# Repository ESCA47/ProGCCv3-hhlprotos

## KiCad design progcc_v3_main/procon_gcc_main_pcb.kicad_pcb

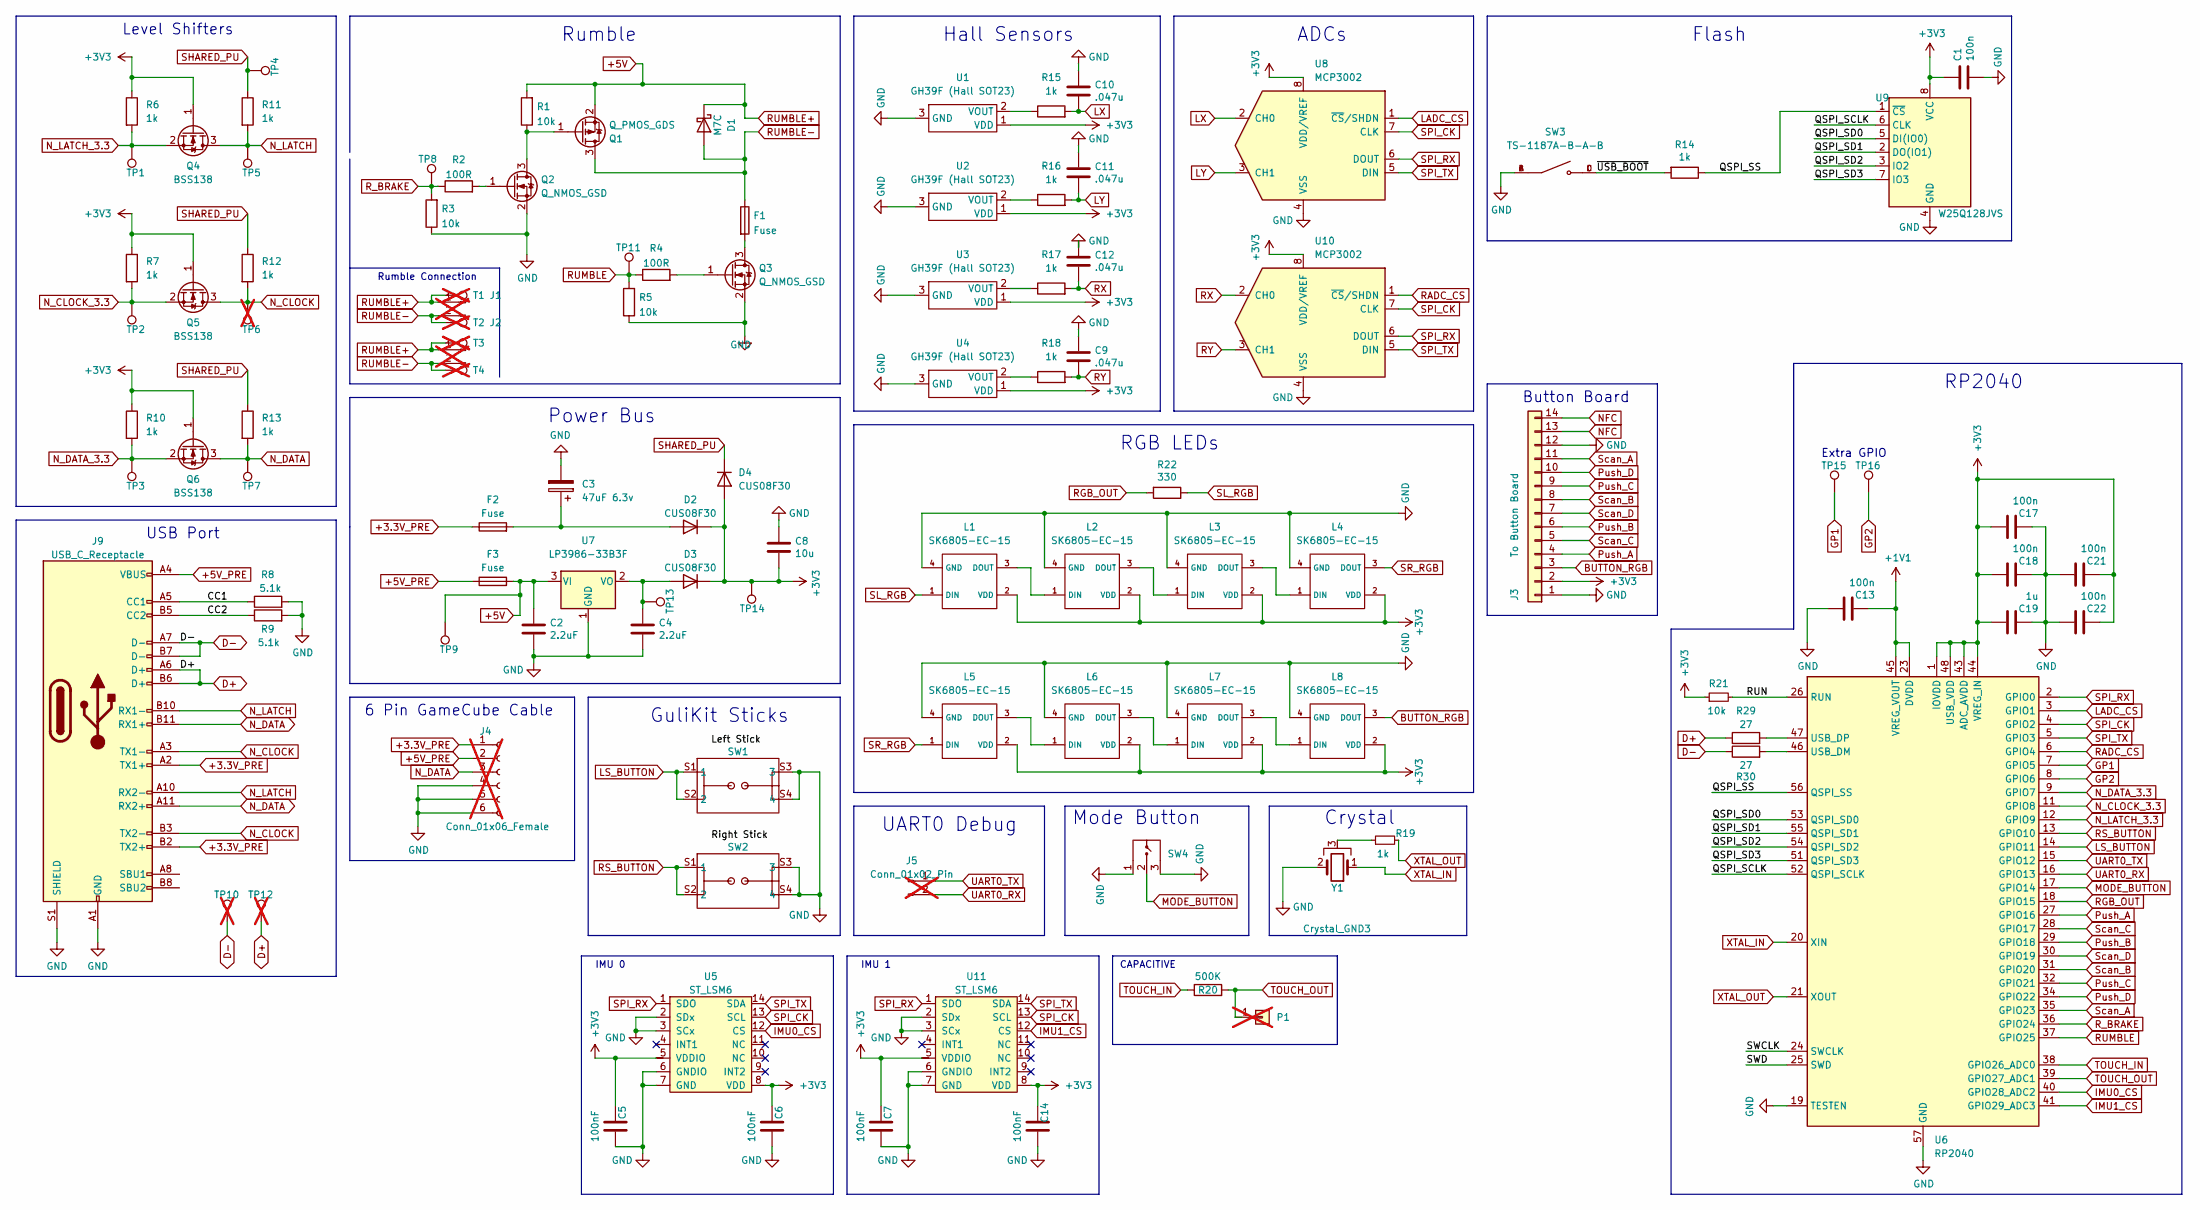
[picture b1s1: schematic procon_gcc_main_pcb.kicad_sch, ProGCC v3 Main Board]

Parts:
C1, C13, C17, C18, C21, C22: 100n; C_0402_1005Metric
C2, C4: 2.2uF; C_0603_1608Metric
C3: 47uF 6.3v; CP_EIA-3216-18_Kemet-A
C5, C6, C7, C14: 100nF; C_0603_1608Metric; LCSC C1525
C8: 10u; C_0603_1608Metric
C9, C10, C11, C12: .047u; C_0603_1608Metric_Pad1.08x0.95mm_HandSolder; LCSC C15849
C19: 1u; C_0402_1005Metric
D1: M7C; D_SOD-123; MPN B5819W SL; LCSC C8598
D2, D3, D4: CUS08F30; D_SOD-323_HandSoldering; MPN CUS08F30
F1, F2, F3: Fuse; Fuse_1206_3216Metric_Pad1.42x1.75mm_HandSolder; LCSC C69680
J1, J2: Rumble; rumble_pins; not fitted
J3: To Button Board; molex_5051101492_14P; MPN molex_5051101492_14P
J4: Conn_01x06_Female; GCC_Header_Straight_1x06_Pitch2.00mm; not fitted
J5: Conn_01x02_Pin; PinHeader_1x02_P2.00mm_Vertical; not fitted
J9: USB_C_Receptacle; Shou Han Type-C 24P QCHT; MPN Shou Han Type-C 24P QCHT
L1, L2, L3, L4, L5, L6, L7, L8: SK6805-EC-15; MPN SK6805-EC-15
P1: Endpoint; PinHeader_1x01_P2.54mm_Vertical; not fitted
Q1: Q_PMOS_GDS; SOT-23; MPN AO3401A; LCSC C15127
Q2, Q3: Q_NMOS_GSD; SOT-23; MPN AO3400A; LCSC C20917
Q4, Q5, Q6: BSS138; SOT-23; MPN BSS138
R1, R3, R5: 10k; R_0402_1005Metric; LCSC C25804
R2, R4: 100R; R_0402_1005Metric; LCSC C22775
R6, R7, R10, R11, R12, R13: 1k; R_0603_1608Metric_Pad0.98x0.95mm_HandSolder
R8, R9: 5.1k; R_0603_1608Metric_Pad0.98x0.95mm_HandSolder
R14, R15, R16, R17, R18, R19: 1k; R_0402_1005Metric
R20: 500K; R_0402_1005Metric; LCSC C11616
R21: 10k; R_0402_1005Metric
R22: 330; R_0402_1005Metric
R29, R30: 27; R_0402_1005Metric
SW1, SW2: GL18_SW; GL18; MPN GL18
SW3: TS-1187A-B-A-B; SW_TS-1187A-B-A-B; PARTREV A0
SW4: TS35CA; MPN TS35CA
T1, T2, T3, T4: 36-8730; KS_8730; not fitted
TP1, TP2, TP3, TP4, TP5, TP7, TP8, TP9, TP11, TP13, TP14, TP15, TP16: TestPoint; TestPoint_Pad_D1.5mm
TP6, TP10, TP12: TestPoint; TestPoint_Pad_D1.5mm; not fitted
U1, U2, U3, U4: GH39F (Hall SOT23); GH39F; MPN GH39F
U5, U11: ST_LSM6; LGA14; MPN LSM6DSRTR; LCSC C784817
U6: RP2040; QFN-56-1EP_7x7mm_P0.4mm_EP3.2x3.2mm; MPN RP2040
U7: LP3986-33B3F; SOT-23; MPN LP3986-33B3F; LCSC Part Number C387689
U8, U10: MCP3002; SOIC-8_3.9x4.9mm_P1.27mm; MPN MCP3002
U9: W25Q128JVS; SOIC-8_5.23x5.23mm_P1.27mm; MPN W25Q128JVS
Y1: Crystal_GND3; Resonator_SMD_Murata_CSTxExxV-3Pin_3.0x1.1mm; MPN CSTNE12M0GH5L000R0

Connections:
+1V1: C13.2, U6.23 (DVDD), U6.45 (VREG_VOUT), U6.50 (DVDD)
+3.3V_PRE: F2.1, J4.1, J9.A2 (TX1+), J9.B2 (TX2+)
+3V3: C1.1, C5.2, C6.2, C7.2, C8.2, C14.2, C17.1, C18.1, C19.1, C21.2, C22.2, D2.1 (K), D3.1 (K), D4.2 (A), J3.2, L1.2 (VDD), L2.2 (VDD), L3.2 (VDD), L4.2 (VDD), L5.2 (VDD), L6.2 (VDD), L7.2 (VDD), L8.2 (VDD), Q4.1 (G), Q5.1 (G), Q6.1 (G), R6.1, R7.1, R10.1, R21.1, TP14.1, U1.1 (VDD), U2.1 (VDD), U3.1 (VDD), U4.1 (VDD), U5.5 (VDDIO), U5.8 (VDD), U6.1 (IOVDD), U6.10 (IOVDD), U6.22 (IOVDD), U6.33 (IOVDD), U6.42 (IOVDD), U6.43 (ADC_AVDD), U6.44 (VREG_IN), U6.48 (USB_VDD), U6.49 (IOVDD), U8.8 (VDD/VREF), U9.8 (VCC), U10.8 (VDD/VREF), U11.5 (VDDIO), U11.8 (VDD)
+5V: C2.1, D1.1 (K), F3.2, J1.1, J2.1, Q1.2 (S), R1.2, T1.1, T3.1, TP9.1, U7.3 (VI)
+5V_PRE: F3.1, J4.2, J9.A4 (VBUS), J9.A9 (VBUS), J9.B4 (VBUS), J9.B9 (VBUS)
/CC1: J9.A5 (CC1), R8.1
/CC2: J9.B5 (CC2), R9.1
/QSPI_SCLK: U6.52 (QSPI_SCLK), U9.6 (CLK)
/QSPI_SD0: U6.53 (QSPI_SD0), U9.5 (DI(IO0))
/QSPI_SD1: U6.55 (QSPI_SD1), U9.2 (DO(IO1))
/QSPI_SD2: U6.54 (QSPI_SD2), U9.3 (IO2)
/QSPI_SD3: U6.51 (QSPI_SD3), U9.7 (IO3)
/QSPI_SS: R14.1, U6.56 (QSPI_SS), U9.1 (~CS)
/RUN: R21.2, U6.26 (RUN)
/SWCLK: U6.24 (SWCLK)
/SWD: U6.25 (SWD)
/~USB_BOOT: R14.2, SW3.C, SW3.D
BUTTON_RGB: J3.3, L8.3 (DOUT)
D+: J9.A6 (D+), J9.B6 (D+), R29.1, TP12.1
D-: J9.A7 (D-), J9.B7 (D-), R30.1, TP10.1
GND: C1.2, C2.2, C3.2, C4.2, C5.1, C6.1, C7.1, C8.1, C9.1, C10.1, C11.1, C12.1, C13.1, C14.1, C17.2, C18.2, C19.2, C21.1, C22.1, J3.1, J3.12, J4.4, J4.5, J4.6, J9.A1 (GND), J9.A12 (GND), J9.B1 (GND), J9.B12 (GND), J9.S1 (SHIELD), L1.4 (GND), L2.4 (GND), L3.4 (GND), L4.4 (GND), L5.4 (GND), L6.4 (GND), L7.4 (GND), L8.4 (GND), Q2.2 (S), Q3.2 (S), R3.1, R5.1, R8.2, R9.2, SW1.S3 (3), SW1.S4 (4), SW2.S3 (3), SW2.S4 (4), SW3.A, SW3.B, SW4.1, SW4.3, U1.3 (GND), U2.3 (GND), U3.3 (GND), U4.3 (GND), U5.2 (SDx), U5.3 (SCx), U5.6 (GNDIO), U5.7 (GND), U6.19 (TESTEN), U6.57 (GND), U7.1 (GND), U8.4 (VSS), U9.4 (GND), U10.4 (VSS), U11.2 (SDx), U11.3 (SCx), U11.6 (GNDIO), U11.7 (GND), Y1.2
GP1: TP15.1, U6.7 (GPIO5)
GP2: TP16.1, U6.8 (GPIO6)
IMU0_CS: U5.12 (CS), U6.40 (GPIO28_ADC2)
IMU1_CS: U6.41 (GPIO29_ADC3), U11.12 (CS)
LADC_CS: U6.3 (GPIO1), U8.1 (~CS/SHDN)
LS_BUTTON: SW1.S1 (1), SW1.S2 (2), U6.14 (GPIO11)
LX: C10.2, R15.2, U8.2 (CH0)
LY: C11.2, R16.2, U8.3 (CH1)
MODE_BUTTON: SW4.2, U6.17 (GPIO14)
NFC: J3.13, J3.14
N_CLOCK: J9.A3 (TX1-), J9.B3 (TX2-), Q5.3 (D), R12.2, TP6.1
N_CLOCK_3.3: Q5.2 (S), R7.2, TP2.1, U6.11 (GPIO8)
N_DATA: J4.3, J9.A11 (RX2+), J9.B11 (RX1+), Q6.3 (D), R13.2, TP7.1
N_DATA_3.3: Q6.2 (S), R10.2, TP3.1, U6.9 (GPIO7)
N_LATCH: J9.A10 (RX2-), J9.B10 (RX1-), Q4.3 (D), R11.2, TP5.1
N_LATCH_3.3: Q4.2 (S), R6.2, TP1.1, U6.12 (GPIO9)
unnamed: C3.1, D2.2 (A), F2.2
unnamed: C4.1, D3.2 (A), TP13.1, U7.2 (VO)
unnamed: L1.3 (DOUT), L2.1 (DIN)
unnamed: L2.3 (DOUT), L3.1 (DIN)
unnamed: L3.3 (DOUT), L4.1 (DIN)
unnamed: L5.3 (DOUT), L6.1 (DIN)
unnamed: L6.3 (DOUT), L7.1 (DIN)
unnamed: L7.3 (DOUT), L8.1 (DIN)
unnamed: Q1.1 (G), Q2.3 (D), R1.1
unnamed: Q2.1 (G), R2.2
unnamed: F1.2, Q3.3 (D)
unnamed: Q3.1 (G), R4.2
unnamed: R19.1, Y1.3
unnamed: R15.1, U1.2 (VOUT)
unnamed: R16.1, U2.2 (VOUT)
unnamed: R17.1, U3.2 (VOUT)
unnamed: R18.1, U4.2 (VOUT)
unnamed: R30.2, U6.46 (USB_DM)
unnamed: R29.2, U6.47 (USB_DP)
Push_A: J3.4, U6.27 (GPIO16)
Push_B: J3.6, U6.29 (GPIO18)
Push_C: J3.9, U6.32 (GPIO21)
Push_D: J3.10, U6.34 (GPIO22)
RADC_CS: U6.6 (GPIO4), U10.1 (~CS/SHDN)
RGB_OUT: R22.2, U6.18 (GPIO15)
RS_BUTTON: SW2.S1 (1), SW2.S2 (2), U6.13 (GPIO10)
RUMBLE: R4.1, R5.2, TP11.1, U6.37 (GPIO25)
RUMBLE-: D1.2 (A), F1.1, J1.2, J2.2, Q1.3 (D), T2.1, T4.1
RX: C12.2, R17.2, U10.2 (CH0)
RY: C9.2, R18.2, U10.3 (CH1)
R_BRAKE: R2.1, R3.2, TP8.1, U6.36 (GPIO24)
SHARED_PU: D4.1 (K), R11.1, R12.1, R13.1, TP4.1
SL_RGB: L1.1 (DIN), R22.1
SPI_CK: U5.13 (SCL), U6.4 (GPIO2), U8.7 (CLK), U10.7 (CLK), U11.13 (SCL)
SPI_RX: U5.1 (SDO), U6.2 (GPIO0), U8.6 (DOUT), U10.6 (DOUT), U11.1 (SDO)
SPI_TX: U5.14 (SDA), U6.5 (GPIO3), U8.5 (DIN), U10.5 (DIN), U11.14 (SDA)
SR_RGB: L4.3 (DOUT), L5.1 (DIN)
Scan_A: J3.11, U6.35 (GPIO23)
Scan_B: J3.8, U6.31 (GPIO20)
Scan_C: J3.5, U6.28 (GPIO17)
Scan_D: J3.7, U6.30 (GPIO19)
TOUCH_IN: R20.1, U6.38 (GPIO26_ADC0)
TOUCH_OUT: P1.1, R20.2, U6.39 (GPIO27_ADC1)
UART0_RX: J5.2, U6.16 (GPIO13)
UART0_TX: J5.1, U6.15 (GPIO12)
XTAL_IN: U6.20 (XIN), Y1.1
XTAL_OUT: R19.2, U6.21 (XOUT)

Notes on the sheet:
Flash
Crystal
IMU 1
Button Board
CAPACITIVE
Extra GPIO
Rumble Connection
IMU 0
RGB LEDs
RP2040
UART0 Debug
GuliKit Sticks
Hall Sensors
Mode Button
Power Bus
ADCs
Level Shifters
Rumble
USB Port
6 Pin GameCube Cable

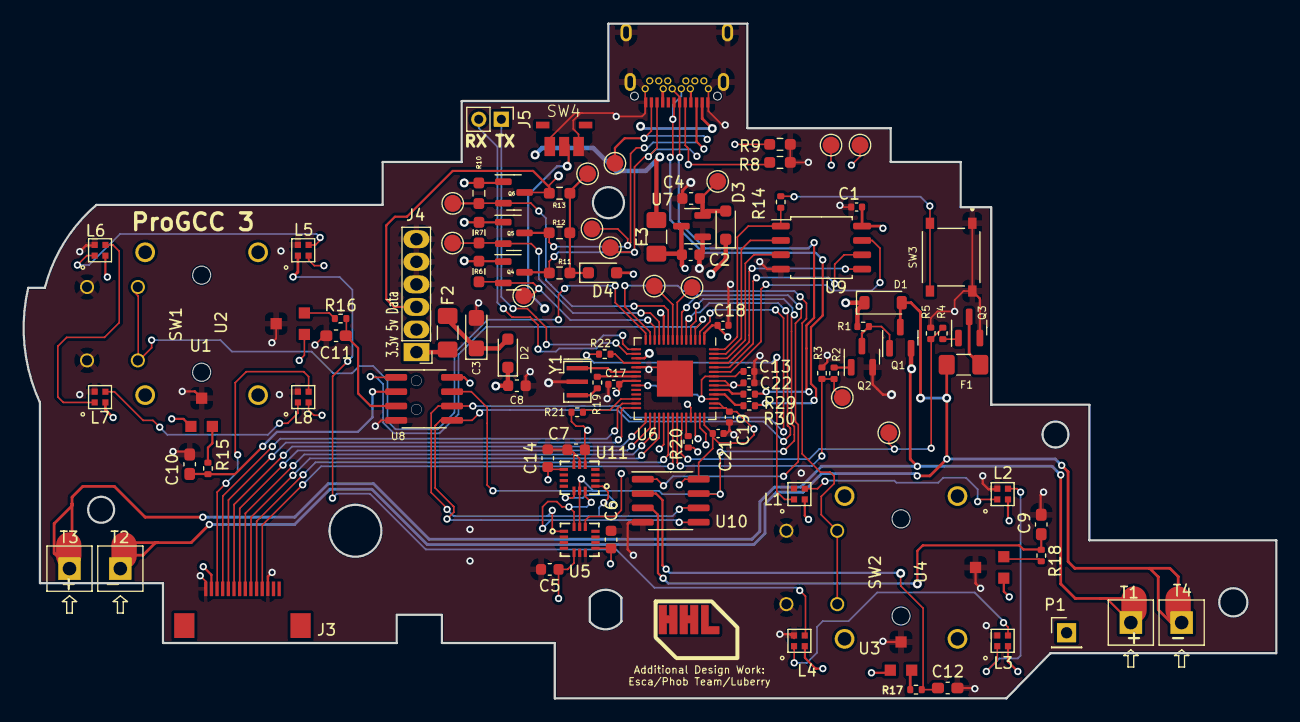
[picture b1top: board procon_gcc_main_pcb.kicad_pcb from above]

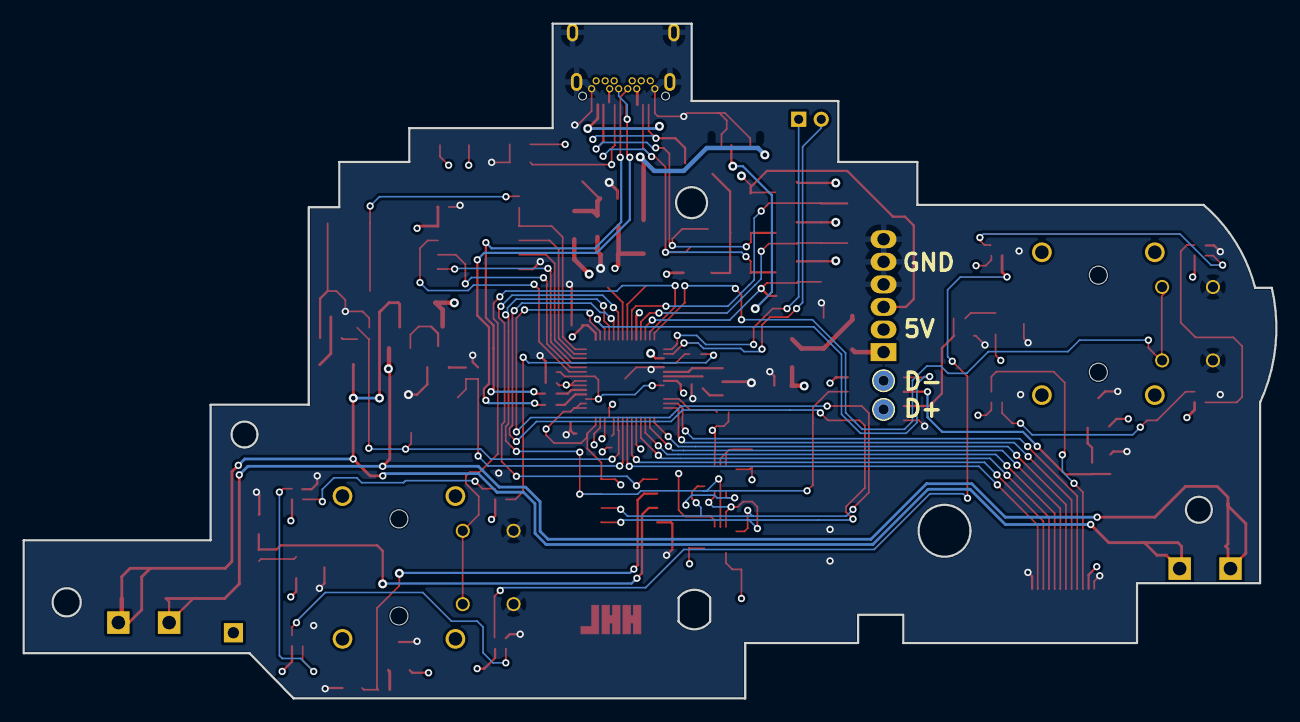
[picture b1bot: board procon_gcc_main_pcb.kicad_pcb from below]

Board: 4 copper layers, 110.9 x 59.7 mm, 107 parts (2 on the bottom side), 82 nets.

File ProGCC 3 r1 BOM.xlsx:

# | Reference | Qty | Value | Footprint | DNP | MPN
1.0 | C1, C13, C17, C18, C21, C22 | 6.0 | 100n | Capacitor_SMD:C_0402_1005Metric
2.0 | C2, C4 | 2.0 | 2.2uF | Capacitor_SMD:C_0603_1608Metric
3.0 | C3 | 1.0 | 47uF 6.3v | Capacitor_Tantalum_SMD:CP_EIA-3216-18_Kemet-A
4.0 | C5, C6, C7, C14 | 4.0 | 100nF | Capacitor_SMD:C_0603_1608Metric
5.0 | C8 | 1.0 | 10u | Capacitor_SMD:C_0603_1608Metric
6.0 | C9, C10, C11, C12 | 4.0 | .047u | Capacitor_SMD:C_0603_1608Metric_Pad1.08x0.95mm_HandSolder
7.0 | C19 | 1.0 | 1u | Capacitor_SMD:C_0402_1005Metric
8.0 | D1 | 1.0 | M7C | Diode_SMD:D_SOD-123 |  | B5819W SL
9.0 | D2, D3, D4 | 3.0 | CUS08F30 | Diode_SMD:D_SOD-323_HandSoldering |  | CUS08F30
10.0 | F1, F2, F3 | 3.0 | Fuse | Fuse:Fuse_1206_3216Metric_Pad1.42x1.75mm_HandSolder
11.0 | J1, J2 | 2.0 | Rumble | progcc_v3:rumble_pins | DNP
12.0 | J3 | 1.0 | To Button Board | progcc_v3:molex_5051101492_14P |  | molex_5051101492_14P
13.0 | J9 | 1.0 | USB_C_Receptacle | progcc_v3:Shou Han Type-C 24P QCHT |  | Shou Han Type-C 24P QCHT
14.0 | L1, L2, L3, L4, L5, L6, L7, L8 | 8.0 | SK6805-EC-15 | progcc_v3:SK6805-EC-15 |  | SK6805-EC-15
15.0 | P1 | 1.0 | Endpoint | Connector_PinHeader_2.54mm:PinHeader_1x01_P2.54mm_Vertical | DNP
16.0 | Q1 | 1.0 | Q_PMOS_GDS | Package_TO_SOT_SMD:SOT-23 |  | AO3401A
17.0 | Q2, Q3 | 2.0 | Q_NMOS_GSD | Package_TO_SOT_SMD:SOT-23 |  | AO3400A
18.0 | Q4, Q5, Q6 | 3.0 | BSS138 | Package_TO_SOT_SMD:SOT-23 |  | BSS138
19.0 | R1, R3, R5, R21 | 4.0 | 10k | Resistor_SMD:R_0402_1005Metric
20.0 | R2, R4 | 2.0 | 100R | Resistor_SMD:R_0402_1005Metric
21.0 | R6, R7, R10, R11, R12, R13 | 6.0 | 1k | Resistor_SMD:R_0603_1608Metric_Pad0.98x0.95mm_HandSolder
22.0 | R8, R9 | 2.0 | 5.1k | Resistor_SMD:R_0603_1608Metric_Pad0.98x0.95mm_HandSolder
23.0 | R14, R15, R16, R17, R18, R19 | 6.0 | 1k | Resistor_SMD:R_0402_1005Metric
24.0 | R20 | 1.0 | 500K | Resistor_SMD:R_0402_1005Metric
25.0 | R22 | 1.0 | 330.0 | Resistor_SMD:R_0402_1005Metric
26.0 | R29, R30 | 2.0 | 27.0 | Resistor_SMD:R_0402_1005Metric
27.0 | SW1, SW2 | 2.0 | GL18_SW | progcc_v3:GL18 |  | GL18
28.0 | SW3 | 1.0 | TS-1187A-B-A-B | progcc_v3:SW_TS-1187A-B-A-B |  | TS-1187A-B-A-B
29.0 | SW4 | 1.0 | ~ | progcc_v3:TS35CA |  | TS35CA
30.0 | T1, T2, T3, T4 | 4.0 | 36-8730 | progcc_v3:KS_8730 | DNP
31.0 | TP1, TP2, TP3, TP4, TP5, TP6, TP7, TP8, TP9, TP10, TP11, TP12, TP13, TP14, TP15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 | 16.0 | TestPoint | TestPoint:TestPoint_Pad_D1.5mm | DNP
32.0 | U1, U2, U3, U4 | 4.0 | GH39F (Hall SOT23) | progcc_v3:GH39F |  | GH39F
33.0 | U5, U11 | 2.0 | ST_LSM6 | progcc_v3:LGA14 |  | LSM6DSRTR
34.0 | U6 | 1.0 | RP2040 | Package_DFN_QFN:QFN-56-1EP_7x7mm_P0.4mm_EP3.2x3.2mm |  | RP2040
35.0 | U7 | 1.0 | LP3986-33B3F | Package_TO_SOT_SMD:SOT-23
36.0 | U8, U10 | 2.0 | MCP3002 | progcc_v3:SOIC-8_3.9x4.9mm_P1.27mm |  | MCP3002
37.0 | U9 | 1.0 | W25Q128JVS | Package_SO:SOIC-8_5.23x5.23mm_P1.27mm |  | W25Q128JVS
38.0 | Y1 | 1.0 | Crystal_GND3 | Crystal:Resonator_SMD_Murata_CSTxExxV-3Pin_3.0x1.1mm |  | CSTNE12M0GH5L000R0

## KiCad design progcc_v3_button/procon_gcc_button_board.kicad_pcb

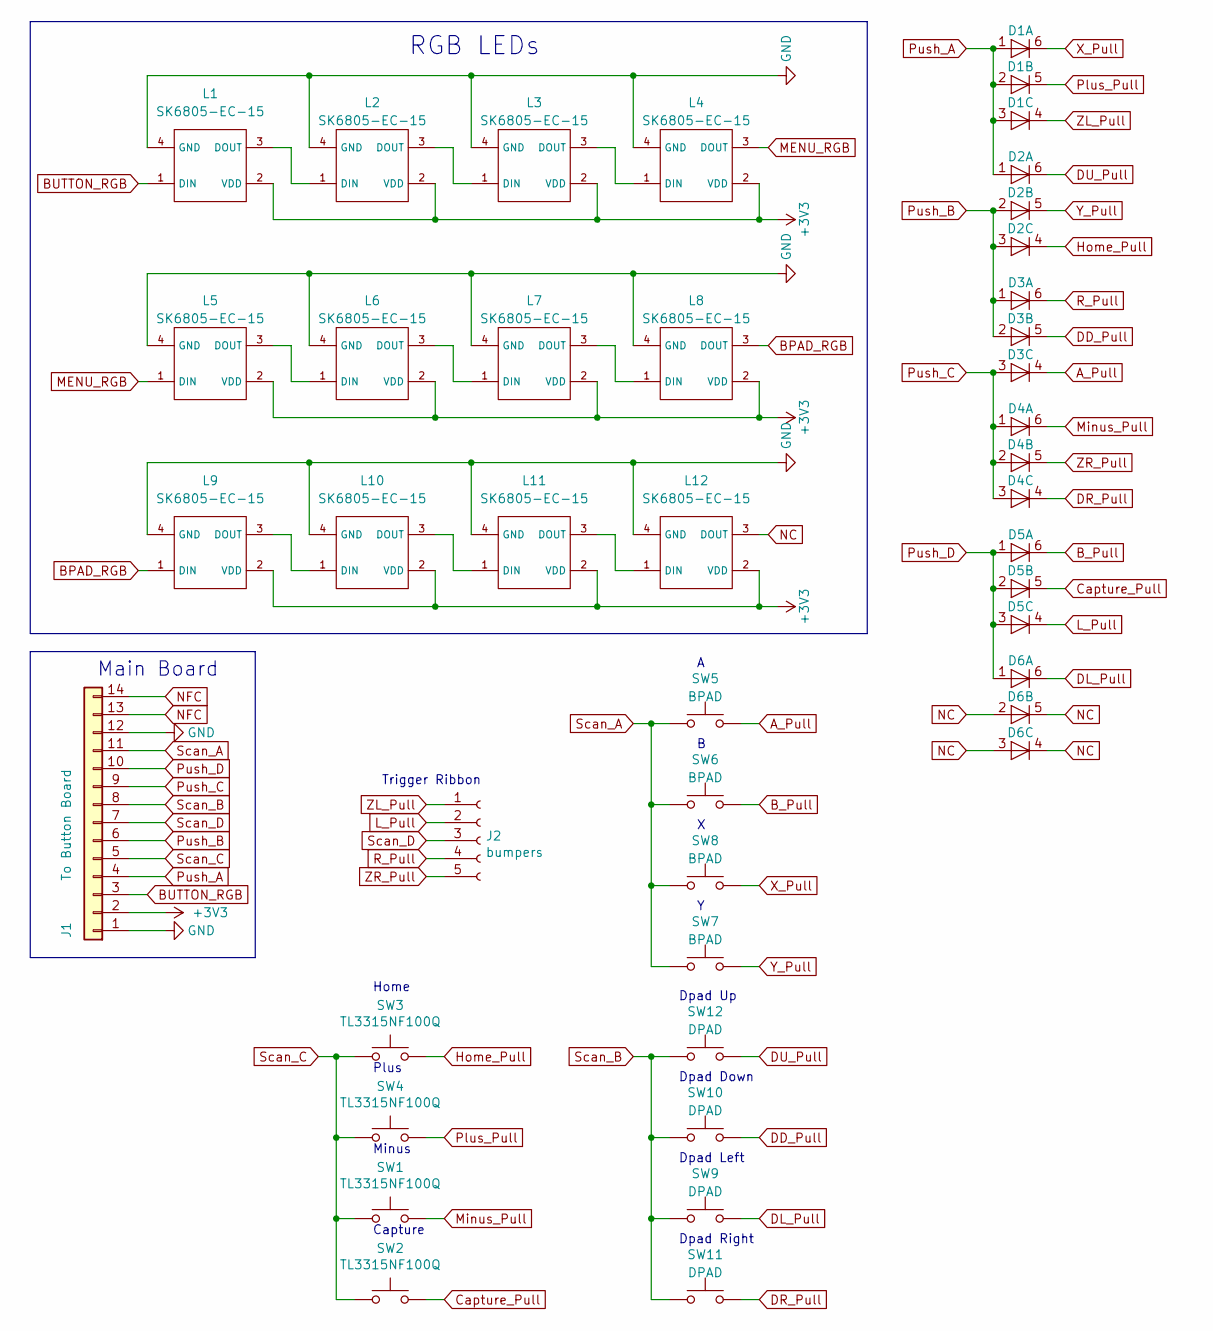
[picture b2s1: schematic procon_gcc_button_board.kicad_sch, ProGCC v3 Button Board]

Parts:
D1, D2, D3, D4, D5, D6: BAS16VY,115; SOT-363_SC-70-6
J1: To Button Board; molex_5051101492_14P
J2: bumpers; molex_5034800540
L1, L2, L3, L4, L5, L6, L7, L8, L9, L10, L11, L12: SK6805-EC-15
SW1, SW2, SW3, SW4: TL3315NF100Q; TL3315NFxxxQ
SW5, SW6, SW7, SW8: BPAD; progcc_bpad
SW9, SW10, SW11, SW12: DPAD; progcc_dpad

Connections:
+3V3: J1.2, L1.2 (VDD), L2.2 (VDD), L3.2 (VDD), L4.2 (VDD), L5.2 (VDD), L6.2 (VDD), L7.2 (VDD), L8.2 (VDD), L9.2 (VDD), L10.2 (VDD), L11.2 (VDD), L12.2 (VDD)
A_Pull: D3.4 (K), SW5.2
BPAD_RGB: L8.3 (DOUT), L9.1 (DIN)
BUTTON_RGB: J1.3, L1.1 (DIN)
B_Pull: D5.6 (K), SW6.2
Capture_Pull: D5.5 (K), SW2.3, SW2.4
DD_Pull: D3.5 (K), SW10.2
DL_Pull: D6.6 (K), SW9.2
DR_Pull: D4.4 (K), SW11.2
DU_Pull: D2.6 (K), SW12.2
GND: J1.1, J1.12, L1.4 (GND), L2.4 (GND), L3.4 (GND), L4.4 (GND), L5.4 (GND), L6.4 (GND), L7.4 (GND), L8.4 (GND), L9.4 (GND), L10.4 (GND), L11.4 (GND), L12.4 (GND)
Home_Pull: D2.4 (K), SW3.3, SW3.4
L_Pull: D5.4 (K), J2.2
MENU_RGB: L4.3 (DOUT), L5.1 (DIN)
Minus_Pull: D4.6 (K), SW1.3, SW1.4
NC: D6.2 (A), D6.3 (A), D6.4 (K), D6.5 (K), L12.3 (DOUT)
NFC: J1.13, J1.14
unnamed: L1.3 (DOUT), L2.1 (DIN)
unnamed: L2.3 (DOUT), L3.1 (DIN)
unnamed: L3.3 (DOUT), L4.1 (DIN)
unnamed: L5.3 (DOUT), L6.1 (DIN)
unnamed: L6.3 (DOUT), L7.1 (DIN)
unnamed: L7.3 (DOUT), L8.1 (DIN)
unnamed: L9.3 (DOUT), L10.1 (DIN)
unnamed: L10.3 (DOUT), L11.1 (DIN)
unnamed: L11.3 (DOUT), L12.1 (DIN)
Plus_Pull: D1.5 (K), SW4.3, SW4.4
Push_A: D1.1 (A), D1.2 (A), D1.3 (A), D2.1 (A), J1.4
Push_B: D2.2 (A), D2.3 (A), D3.1 (A), D3.2 (A), J1.6
Push_C: D3.3 (A), D4.1 (A), D4.2 (A), D4.3 (A), J1.9
Push_D: D5.1 (A), D5.2 (A), D5.3 (A), D6.1 (A), J1.10
R_Pull: D3.6 (K), J2.4
Scan_A: J1.11, SW5.1, SW6.1, SW7.1, SW8.1
Scan_B: J1.8, SW9.1, SW10.1, SW11.1, SW12.1
Scan_C: J1.5, SW1.1, SW1.2, SW2.1, SW2.2, SW3.1, SW3.2, SW4.1, SW4.2
Scan_D: J1.7, J2.3
X_Pull: D1.6 (K), SW8.2
Y_Pull: D2.5 (K), SW7.2
ZL_Pull: D1.4 (K), J2.1
ZR_Pull: D4.5 (K), J2.5

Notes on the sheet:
Plus
Capture
Dpad Right
Main Board
Dpad Up
Dpad Down
Trigger Ribbon
Dpad Left
Home
Minus
RGB LEDs

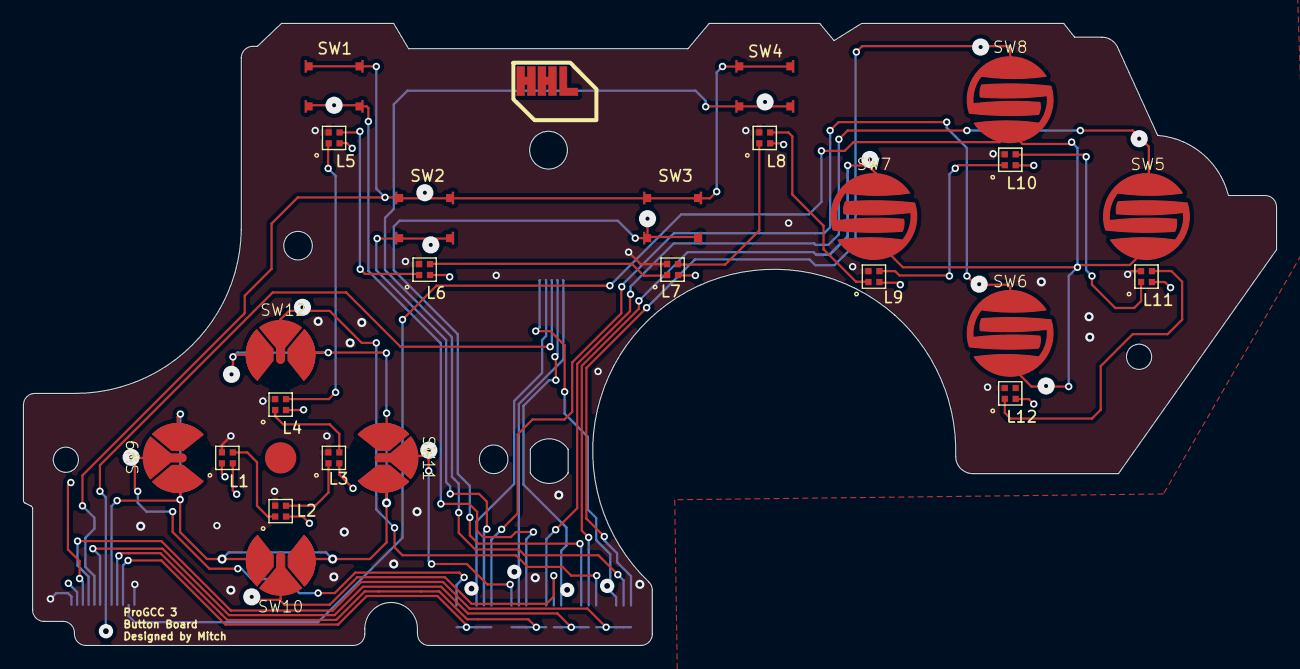
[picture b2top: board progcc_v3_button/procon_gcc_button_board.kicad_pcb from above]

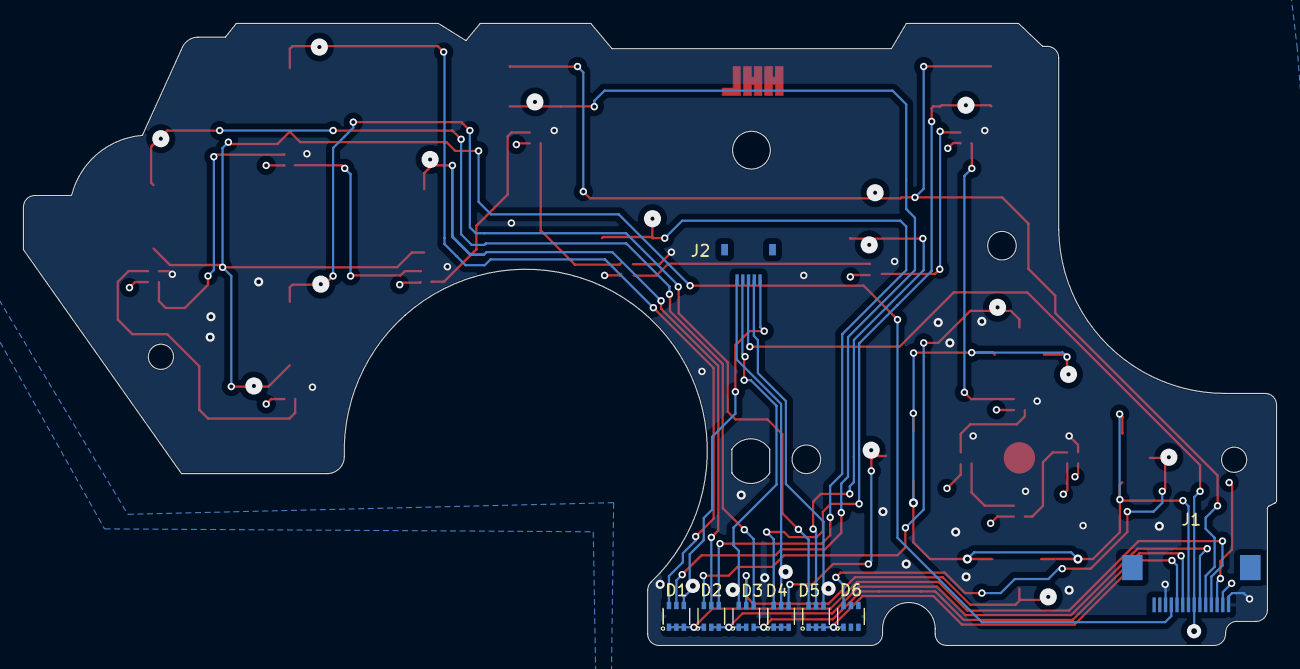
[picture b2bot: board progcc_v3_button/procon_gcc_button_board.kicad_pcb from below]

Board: 4 copper layers, 109.4 x 54.3 mm, 32 parts (8 on the bottom side), 40 nets.

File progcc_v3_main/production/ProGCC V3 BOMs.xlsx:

Id | Designator | Footprint | Quantity | Designation | Supplier and ref | Part # | Notes
1.0 | SW4,SW2,SW1,SW3 | TL3315NFxxxQ | 4.0 | TL3315NF100Q |  | TL3315NF100Q
2.0 | L6,L4,L2,L12,L5,L9,L1,L3,L11,L7,L10,L8 | SK6805-EC-15 | 12.0 | SK6805-EC-15 |  | SK6805-EC-15
3.0 | SW7,SW5,SW6,SW8 | progcc_bpad | 4.0 | BPAD |  |  | DNP no solder.
4.0 | D2,D5,D4,D6,D3,D1 | SOT-363_SC-70-6 | 6.0 | BAS16VY,115 |  | BAS16VY,115
5.0 | J2 | molex_5051100592_5P | 1.0 | bumpers |  | molex_5051100592_5P
6.0 | J1 | molex_5051101492_14P | 1.0 | To Button Board |  | molex_5051101492_14P

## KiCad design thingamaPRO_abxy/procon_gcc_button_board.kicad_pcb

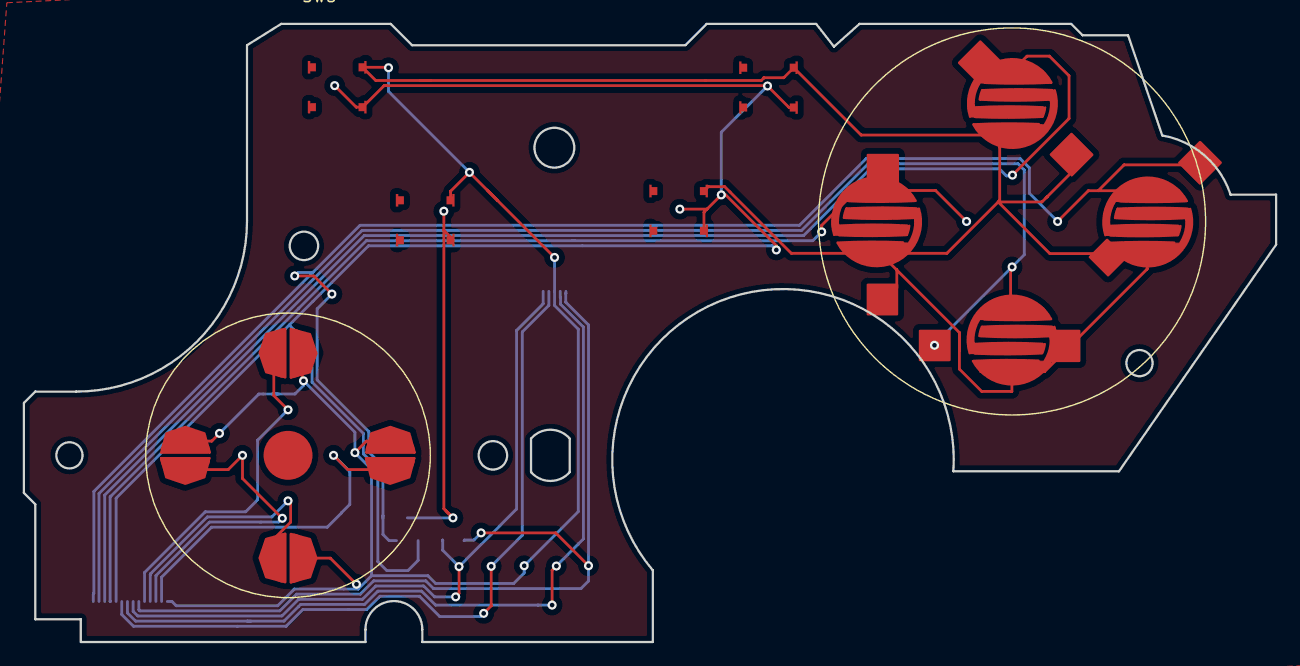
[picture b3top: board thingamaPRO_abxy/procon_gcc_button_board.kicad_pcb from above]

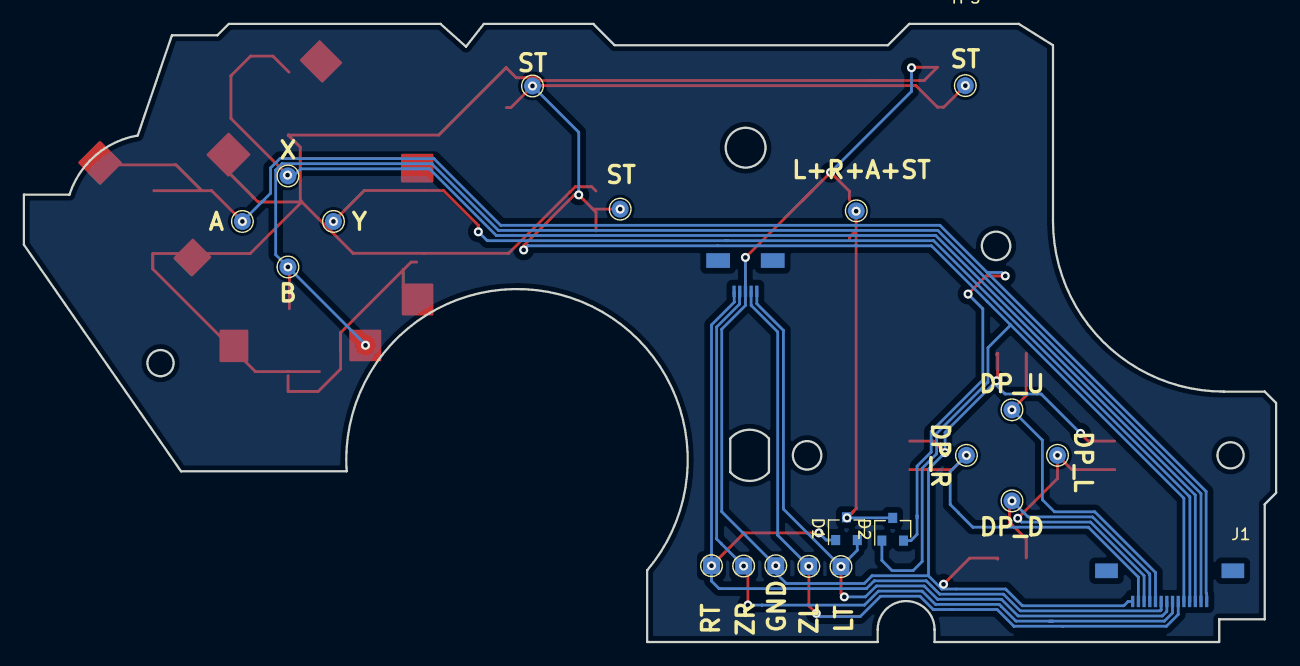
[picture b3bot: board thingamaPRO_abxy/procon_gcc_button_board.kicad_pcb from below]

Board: 2 copper layers, 110.0 x 54.3 mm, 31 parts (21 on the bottom side), 15 nets.

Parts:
D1, D2: BAV70; SOT-23
J1: Button Board; molex_5051101492_14P
J2: bumpers; molex_5051100592_5P
Ref**: Val**; ABXY_Contact_Omron_Switch
Ref**#2, Ref**#3, Ref**#4: Val**; ABXY_Contact_Omron_Switch
SW1: procon_abxy
SW2: procon_dpad
SW3, SW4, SW5, SW6: TL3315NF100Q; TL3315NFxxxQ
TP1, TP2, TP3, TP4, TP5, TP5#2, TP5#3, TP5#4, TP6, TP7, TP8, TP9, TP10, TP11, TP12, TP13, TP14: TestPoint; TestPoint_Pad_D1.5mm

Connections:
BB_BTN_A: D2.2 (A), J1.1, Ref**#4.2, SW1.1 (A), TP1.1
BB_BTN_B: J1.2, Ref**.2, SW1.2 (B), TP2.1
BB_BTN_DP_D: J1.11, SW2.3 (DP_D), TP11.1
BB_BTN_DP_L: J1.12, SW2.4 (DP_L), TP12.1
BB_BTN_DP_R: J1.13, SW2.2 (DP_R), TP13.1
BB_BTN_DP_U: J1.10, SW2.1 (DP_U), TP10.1
BB_BTN_LT: D1.2 (A), J1.8, J2.1, TP8.1
BB_BTN_RT: D1.1 (A), J1.9, J2.5, TP9.1
BB_BTN_ST: D2.1 (A), J1.5, SW3.1, SW5.1, SW6.1, TP5.1, TP5#2.1, TP5#3.1, TP5#4.1
BB_BTN_X: J1.3, SW1.4 (X), TP3.1
BB_BTN_Y: J1.4, SW1.3 (Y), TP4.1
BB_BTN_ZL: J1.6, J2.2, TP6.1
BB_BTN_ZR: J1.7, J2.4, TP7.1
GND: J1.14, J2.3, Ref**#2.2, Ref**#3.2, SW1.GND, SW2.GND, SW3.2, SW4.2, SW5.2, SW6.2, TP14.1
unnamed: D1.3 (K), D2.3 (K), SW4.1

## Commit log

2023-03-06 copypastefromdesktop
2023-03-09 added screw in terminals
    pushing this to have a branch before the mapping changes
2023-03-09 Matrix Rewire for front boards
    Swapped from direct to a matrix layout to support oem front boards
2023-03-11 Update naming schema
2023-03-11 Update gitignore
2023-03-11 Remove backups
2023-03-11 all libraries fixed+hole positioning changes
    fixed the screw points to be more accurate as well add a front bracket keepout to help with the future reroute
2023-03-19 Moved components+setup for reroute
    hopefully fixed bad library dependencies too
2023-03-19 Fix library folder pathings
2023-03-20 Major reorganization
    Unlink local folder name schema
    Organize libs into proper folder structure
2023-04-05 better placement of componenets+4layer change
    rough placement of everything/start of reroute
2023-04-12 Lots of schematic changes and upgrades
    Good luck :P
2023-04-14 some schematic fixes+some positioning
2023-04-15 Schematic finalization
2023-04-15 More schematic fixes
    Added some more schematic items, grouped RP2040 with caps on PCB.
2023-04-24 some positioning changes+fP adjustments
2023-04-27 USB C routing area
2023-05-03 major routing
    most of the board is routed minus a couple bits
2023-05-05 Kicad 7 and Routing
    More routing done
    Updated to Kicad 7 file types
2023-05-06 Update button board
2023-05-06 Update Pads and DRC
2023-05-06 Production files
2023-05-06 Remove old production
2023-05-06 Remove unneeded bom
2023-05-06 Remove more unneeded files.
2023-05-08 Update part #
2023-05-09 Fixed missing trace
    Missing trace and N Channel mosfet fix
2023-05-26 Update proto
    - Update stick position
    - Adjust some screw position slightly
    - Fix schematic for Crystal and Rumble
2023-05-27 Major updates
    -Revised button board outline
    -Added IMU for motion
    -Cleaned up traces on main board
    -Add test pads to button board
2023-05-27 Add excel bom
2023-05-27 Fix Stick positions (More!)
2023-05-27 Update drill map
2023-06-02 remove unused lib
2023-06-07 50 qty test run update
2023-06-27 Update production files
